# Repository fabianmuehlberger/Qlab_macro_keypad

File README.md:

# Qlab_macro_keypad
macro keypad for controlling Qlab with cherry keys and encoder using a KB2040

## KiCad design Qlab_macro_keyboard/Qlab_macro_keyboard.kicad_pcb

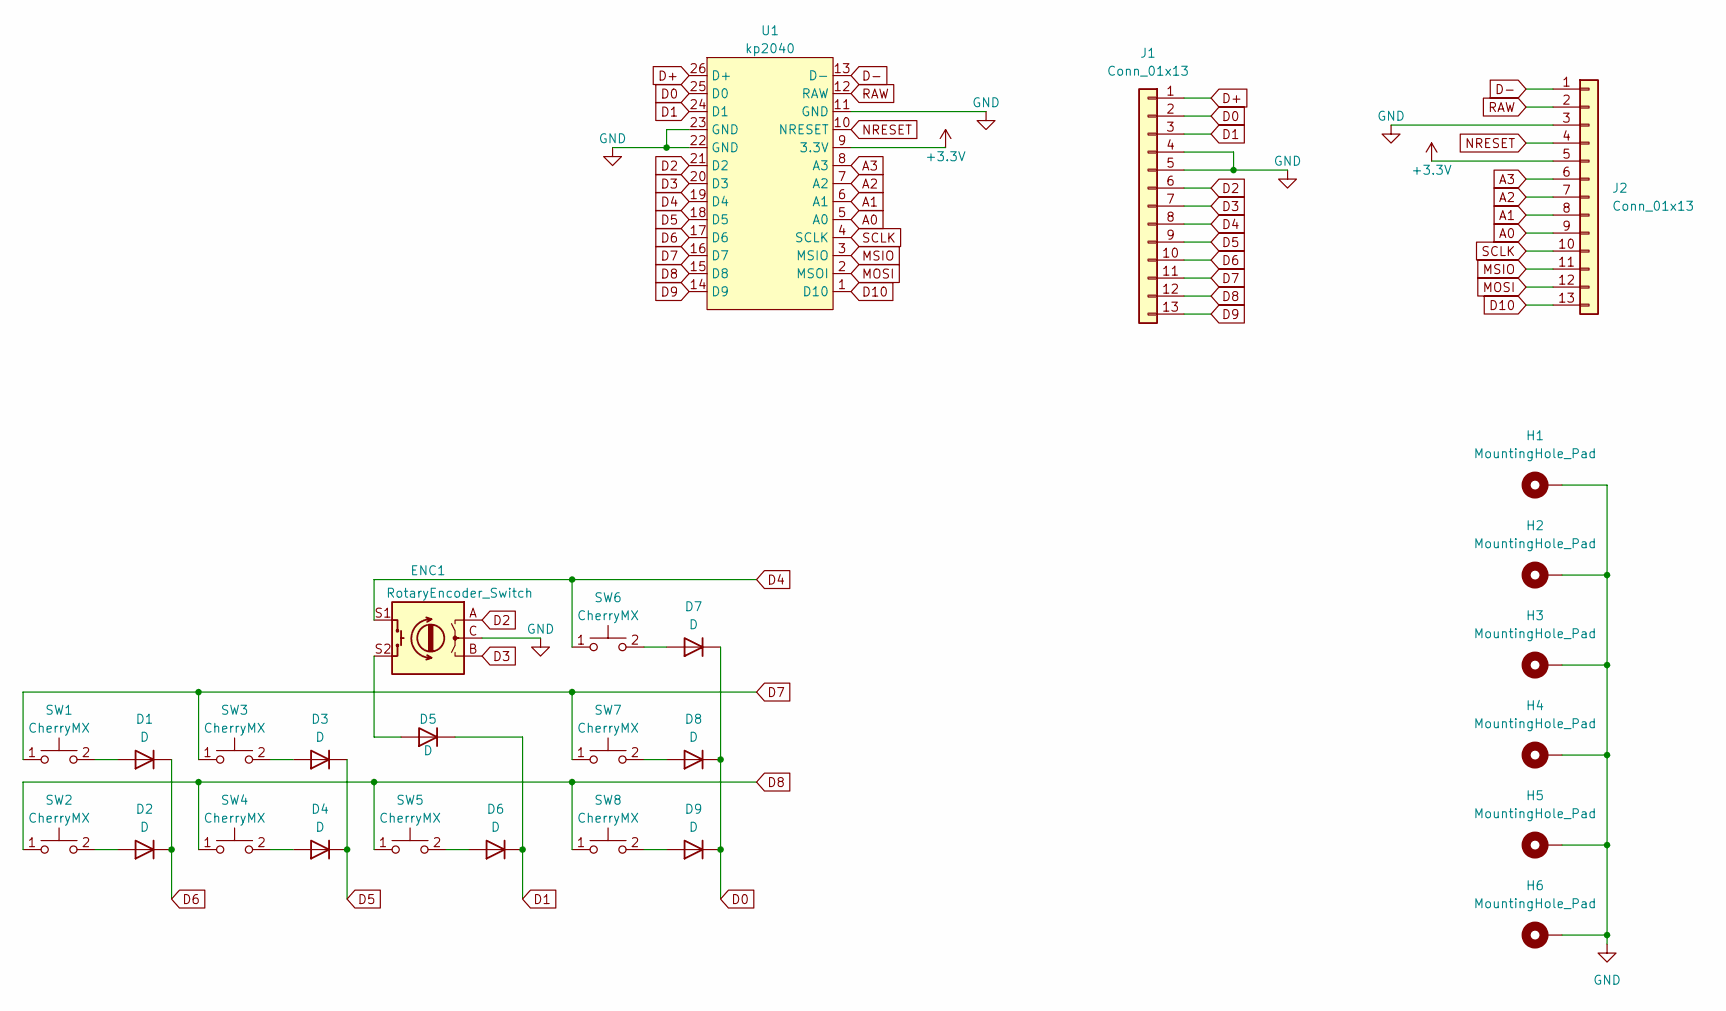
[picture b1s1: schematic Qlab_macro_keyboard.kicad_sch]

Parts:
D1, D2, D3, D4, D5, D6, D7, D8, D9: D; D_1210_3225Metric
ENC1: RotaryEncoder_Switch; RotaryEncoder_Alps_EC11E-Switch_Vertical_H20mm
H1, H2, H3, H4, H5, H6: MountingHole_Pad; MountingHole_3.2mm_M3_DIN965_Pad
J1, J2: Conn_01x13; PinHeader_1x13_P2.54mm_Vertical
SW1, SW2, SW3, SW4: CherryMX; CherryMX_1.00u
SW5, SW6, SW7, SW8: CherryMX; CherryMX_2.00u_StabWireBottom
U1: kp2040

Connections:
+3V3: J2.5, U1.9 (3.3V)
A0: J2.9, U1.5 (A0)
A1: J2.8, U1.6 (A1)
A2: J2.7, U1.7 (A2)
A3: J2.6, U1.8 (A3)
D0: D7.1 (K), D8.1 (K), D9.1 (K), J1.2, U1.25 (D0)
D1: D5.1 (K), D6.1 (K), J1.3, U1.24 (D1)
D2: ENC1.A, J1.6, U1.21 (D2)
D3: ENC1.B, J1.7, U1.20 (D3)
D4: ENC1.S1, J1.8, SW6.1, U1.19 (D4)
D5: D3.1 (K), D4.1 (K), J1.9, U1.18 (D5)
D6: D1.1 (K), D2.1 (K), J1.10, U1.17 (D6)
D7: J1.11, SW1.1, SW3.1, SW7.1, U1.16 (D7)
D8: J1.12, SW2.1, SW4.1, SW5.1, SW8.1, U1.15 (D8)
D9: J1.13, U1.14 (D9)
D10: J2.13, U1.1 (D10)
D+: J1.1, U1.26 (D+)
D-: J2.1, U1.13 (D-)
GND: ENC1.C, H1.1, H2.1, H3.1, H4.1, H5.1, H6.1, J1.4, J1.5, J2.3, U1.11 (GND), U1.22 (GND), U1.23 (GND)
MOSI: J2.12, U1.2 (MSOI)
MSIO: J2.11, U1.3 (MSIO)
NRESET: J2.4, U1.10 (NRESET)
unnamed: D1.2 (A), SW1.2
unnamed: D2.2 (A), SW2.2
unnamed: D3.2 (A), SW3.2
unnamed: D4.2 (A), SW4.2
unnamed: D5.2 (A), ENC1.S2
unnamed: D6.2 (A), SW5.2
unnamed: D7.2 (A), SW6.2
unnamed: D8.2 (A), SW7.2
unnamed: D9.2 (A), SW8.2
RAW: J2.2, U1.12 (RAW)
SCLK: J2.10, U1.4 (SCLK)

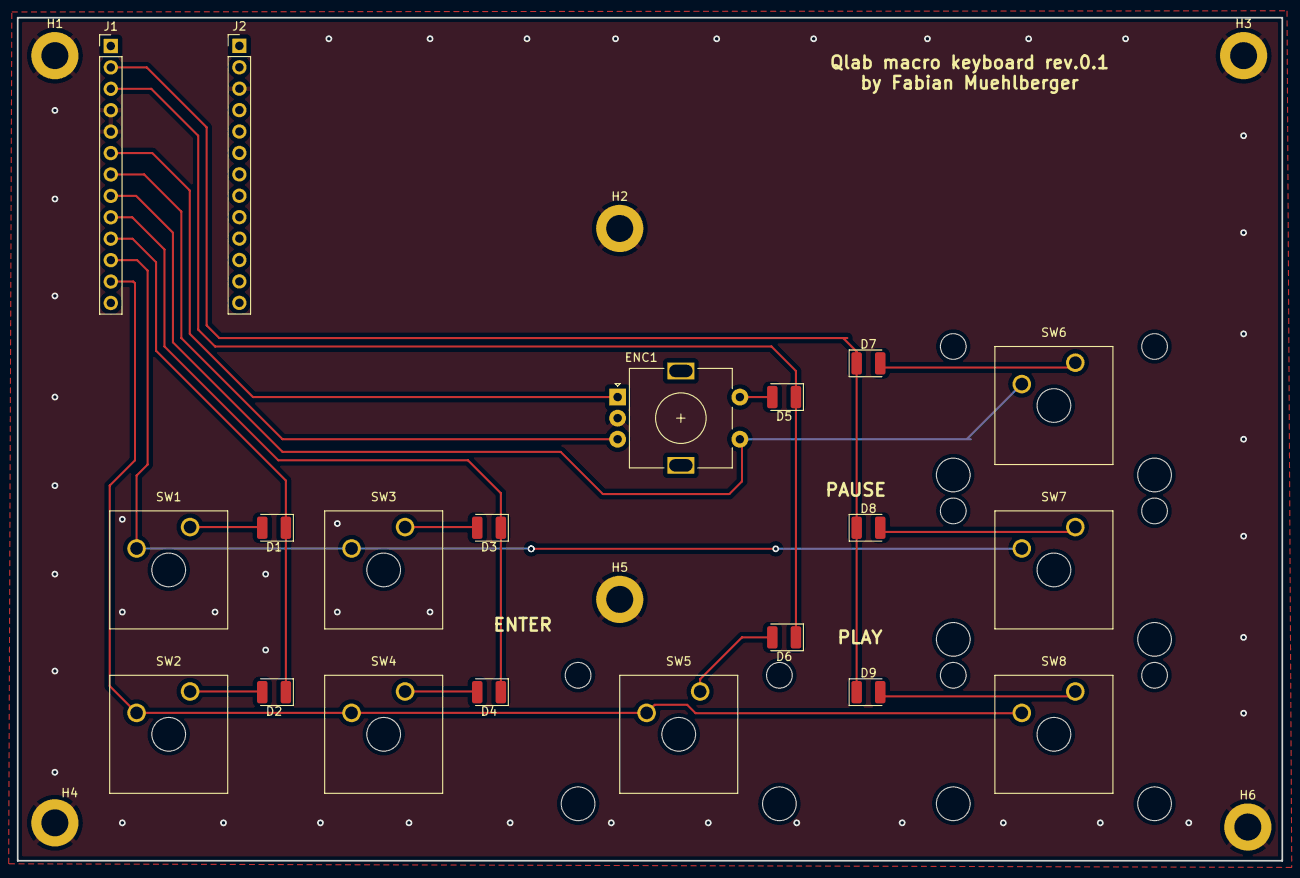
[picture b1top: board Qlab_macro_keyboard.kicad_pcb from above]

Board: 2 copper layers, 150.0 x 100.0 mm, 26 parts (0 on the bottom side), 19 nets.
